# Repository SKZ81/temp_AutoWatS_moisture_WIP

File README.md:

# Routing a custom capacitive "i2c-moisture_sensor"

**NOTE:** this is **NOT** an entirely new design, just a new layout/routing of an open source concept.

## Introduction

### Context

**@Miceuz** has released a few open source/hardware projects related to sensing moisture level in soil, using capacitive techniques to avoid corrosition of the sensor's tracks.

For instance the [Chirp!](https://github.com/Miceuz/PlantWateringAlarm), that has been heavily cloned...

Personnaly I came across this project "thanks to" **AZ Delivery** (a german shop on Amazon. I don't recommand them at all), that had a deal for 3rd party testers : 1) buy a thing 2) write a review 3) get a full refund.

But let's the gnome explain that process better than I could :

I'm still waiting for step 3 completion.

Note that the [Chirp!](https://github.com/Miceuz/PlantWateringAlarm) is intented to work as a standalone item : it embeds a battery and a buzzer to autonomously report low watering level of the plant soil. It even measures lighting level using an impressive technique implying applying a reverse voltage on the LED that otherwise is used to indicate the [Chirp!](https://github.com/Miceuz/PlantWateringAlarm)

AZ Delivery claims the item is "delivered with an ebook" (I knew i meant : you'll get an email with the PDF URL... If you're lucky, or you can search by yourself on our website...)
Just for reference [here is the amazon UK webpage for this item](https://www.amazon.co.uk/AZDelivery-Plant-Watering-Alerter-Parent/dp/B086V7ZKHF?th=1)

But this is "Fake Ad", as I found myself actually desperate for any documentation on how to speak to the device. Then I found an obscure comment about the [Chirp!](https://github.com/Miceuz/PlantWateringAlarm) that I did not understood at first. Indeed, the phrasing didn't make it obvious that "**Chirp!**" was designating a (OSH) project... But when it came out that it was my last clue, I gave it a chance in a SE, and taadaaaa !

Here we we'll more focus on cloning the i²c slave version(sol called "[i2c-moisture-sensor](https://github.com/Miceuz/i2c-moisture-sensor)".

** NB: ** on my work station I had to checkout commit `f0ea6744f6da897fee02f7d46b23bc4d33b74620` (2020/07/22) to get an openable .kicad_pcb file.

Both designs are mainly equivalent, firmwares are also very similar. [1]

### Goals

* Clone this board (it's OSH)
* PCBA print them
* Use them in a cluster of plants

### Motivations

You'll ask me : but why don't you buy a bunch of them to @Miceuz ?

* Because I want a lot of them, given the unit price, better PCBA them

So why re-routing ?

* To learn more of KiCAD
* For the challenge / the pride
* To substitute parts/footprints with cheap "basic parts" from PCBA

And why this document ?

* This is a synthesis of what I learned / understood
* It should allow me to ask for some help/advices
* I may write a blog article out of it afterward

## Work Achieved So Far...

### Schematics

I just copied it, by hand, from the schematics of master/HEAD in [i2c-moisture-sensor](https://github.com/Miceuz/i2c-moisture-sensor)

The core of the circuit is an **AtTiny441**, so I guess most concepts are familiar to readers from #avr(s).

A few notes, though :

* This weird symbol is just a custom crystal, I needed a different pinout,
* 3x2 ISP is for in-lab flashing, nothing will be soldered in-field,
* 4x1 connector is for i²c in-field operation (should be hard-soldered... Let's me think of a few mechanical contrains before [2]).
* LED is for indicating work BUT ALSO for ambient light level measurement !
* Please note that "SENSOR_TRACK" label...

### Understanding operation principle

As I just copied the work, let's link to the [original writing](https://wemakethings.net/2012/09/26/capacitance_measurement/).

As a summary : just send a square wave into a cap formed in part by the soil, and measure its relative variations to get info about the soil moisture.

It seems that it's the operation principle used by the [Chirp!](https://github.com/Miceuz/PlantWateringAlarm) clone I bought. Unsure about the newer one selled by @Miceuz [1].

The schematics above got an upgrade : I can't explain the "why" but it was not enough to measure the high peak of charge to determine the soil capacitance, but you need to offset it at the "low point".

I'm pretty sure (despite [1]) that the **Chirpi!** only uses one line to probe the capacitance...

As a "proof", look at this `get_capacitance()` version :

[Source code on Github](https://github.com/Miceuz/PlantWateringAlarm/blob/master/src/main.c#L147)

It looks "in phase" with the Operation Principle described and linked above.

In regard, in [i2c-moisture-sensor](https://github.com/Miceuz/i2c-moisture-sensor/), this function becomes :
https://github.com/Miceuz/i2c-moisture-sensor/blob/master/src/main.c#L111

Beyond the excitation signal problem (see below), the comparision of codes sounds to explain the hardware variations.

### Routing

Here is the work I did in KiCAD's pcbnew from this schematics.

#### Main circuit

#### Sensor Track

This track is supposed to form a sensible capacitor when burried in soil.

## My Questions

### Schottky diodes

I spent a few time comparing the datasheet of the recommanded diode, with the cheap "basic parts" stock of the PCBA I order from.

To me, the exact rating of the diode here is not really relevant if you think you it as a current rectifier, no matter what is Vdrop : this will/can change the calibration values, but doesn't "hurt" the principle of operation : the 1nF capacitors C5 abd C6 will "display" a given voltage, function of the exponential charge/discharge with time factor is itself function of the soil+sensor capacitice...

Right ??

### Sensor Track 1 My "Design Rules"

I'm not sure how the topology of this traces will influence the capacitance. Once again, my beleif is that it will just inflence calibration factors.

I tried to copy the original PCN design as wel as the schematics, but I just don't speak Maxwelian, eventhough I have some insights...

### Quartz Shielding (?)

What about my crystal routing and sheilding (both under and around ?)

I tried to route any switching signal away from it...

### Excitation Signal Ignition

That is the "best" mystery in the field..
I can cope with my lack of EE skillz but when it comes to software... AVR software futhermore I assume I master it. Not aal bits, but, mostly.

Just like this closed issue mention : "[where is the code ?](https://github.com/Miceuz/i2c-moisture-sensor/issues/29)"

## Conclusion

I'm pretty sure the design I copied is reat, and I hope my layout is coherent. I'm just just freaking out myself how this shit is supposed to operate...

[1] **TODO :** check HEAD/master last version of Chirp!
[2] i²c cable connectors / insertion
[3] Add a DEBUG (analog voltages) pad on the PCB
[4] Lower down that silkscreen line and/or shorten some tracks (sensor included)

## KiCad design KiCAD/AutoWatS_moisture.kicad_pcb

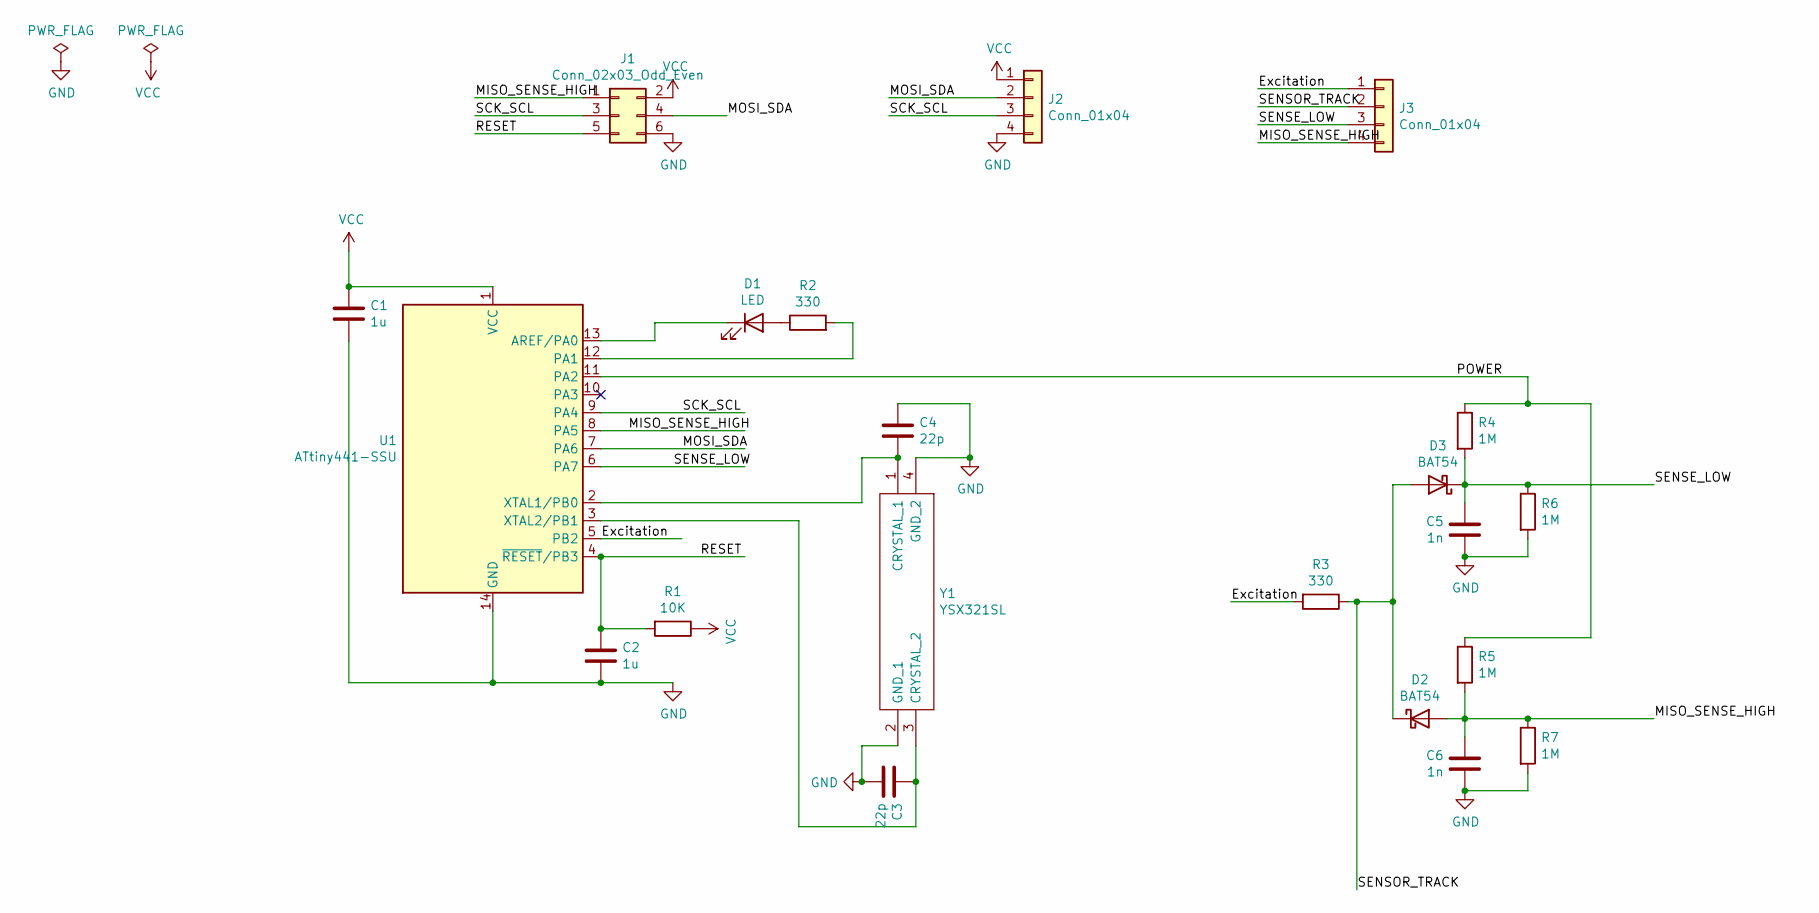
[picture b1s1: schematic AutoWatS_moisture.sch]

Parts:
C1, C2: 1u; C_0805_2012Metric; LCSC Part C28323
C3, C4: 22p; C_0805_2012Metric; LCSC Part C1804
C5, C6: 1n; C_0805_2012Metric; LCSC Part C46653
D1: LED; LED_0805_2012Metric; LCSC Part C34499
D2: BAT54; D_SOD-123; LCSC C8598
D3: BAT54; D_SOD-123; LCSC Part C8598
J1: Conn_02x03_Odd_Even; PinHeader_2x03_P2.54mm_Vertical
J2, J3: Conn_01x04; PinHeader_1x04_P2.54mm_Vertical
R1: 10K; R_0805_2012Metric; LCSC Part C17414
R2, R3: 330; R_0805_2012Metric; LCSC Part C17630
R4, R5, R6, R7: 1M; R_0805_2012Metric; LCSC Part C17514
U1: ATtiny441-SSU; SOIC-14_3.9x8.7mm_P1.27mm; LCSC Part C145746
Y1: YSX321SL; Manufacturer_Part_Number YSX321SL; LCSC Part C13738

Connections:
/Excitation: J3.1, R3.2, U1.5 (PB2)
/MISO_SENSE_HIGH: C6.2, D2.2 (A), J1.1, J3.4, R5.2, R7.1, U1.8 (PA5)
/MOSI_SDA: J1.4, J2.2, U1.7 (PA6)
/POWER: R4.1, R5.1, U1.11 (PA2)
/RESET: C2.1, J1.5, R1.2, U1.4 (~RESET~/PB3)
/SCK_SCL: J1.3, J2.3, U1.9 (PA4)
/SENSE_LOW: C5.2, D3.1 (K), J3.3, R4.2, R6.1, U1.6 (PA7)
/SENSOR_TRACK: D2.1 (K), D3.2 (A), J3.2, R3.1
GND: C1.2, C2.2, C3.2, C4.1, C5.1, C6.1, J1.6, J2.4, R6.2, R7.2, U1.14 (GND), Y1.2 (GND_1), Y1.4 (GND_2)
unnamed: C3.1, U1.3 (XTAL2/PB1), Y1.3 (CRYSTAL_2)
unnamed: C4.2, U1.2 (XTAL1/PB0), Y1.1 (CRYSTAL_1)
unnamed: D1.1 (K), U1.13 (AREF/PA0)
unnamed: D1.2 (A), R2.1
unnamed: R2.2, U1.12 (PA1)
VCC: C1.1, J1.2, J2.1, R1.1, U1.1 (VCC)

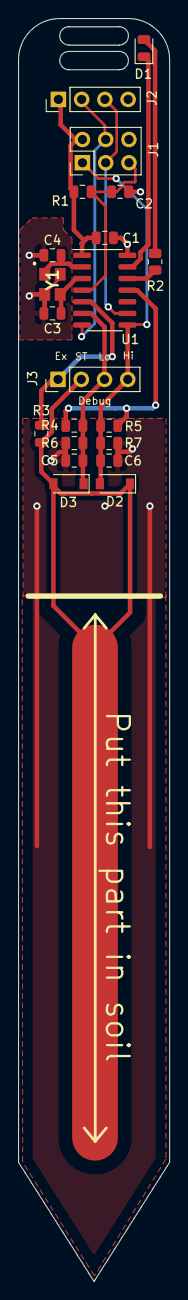
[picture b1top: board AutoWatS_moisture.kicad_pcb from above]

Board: 2 copper layers, 16.5 x 138.0 mm, 21 parts (0 on the bottom side), 15 nets.

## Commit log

2020-11-16 Fix Xtal footprint ref
2020-11-16 Added debug port, silk info and changed the layout a bit
2020-11-16 Updated doc
2020-11-18 Added panel show case image
